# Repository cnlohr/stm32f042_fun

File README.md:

# stm32f042_fun

My fun repo for the STM32f042.  Feel free to rifle through.  All the projects are incomplete, but mostly work.

Check out my IO list: https://docs.google.com/spreadsheets/d/1DyMCKiVg4tmwGgn1U_OD7lgiobow0eRoh-zJ0Q15YpQ/edit?usp=sharing

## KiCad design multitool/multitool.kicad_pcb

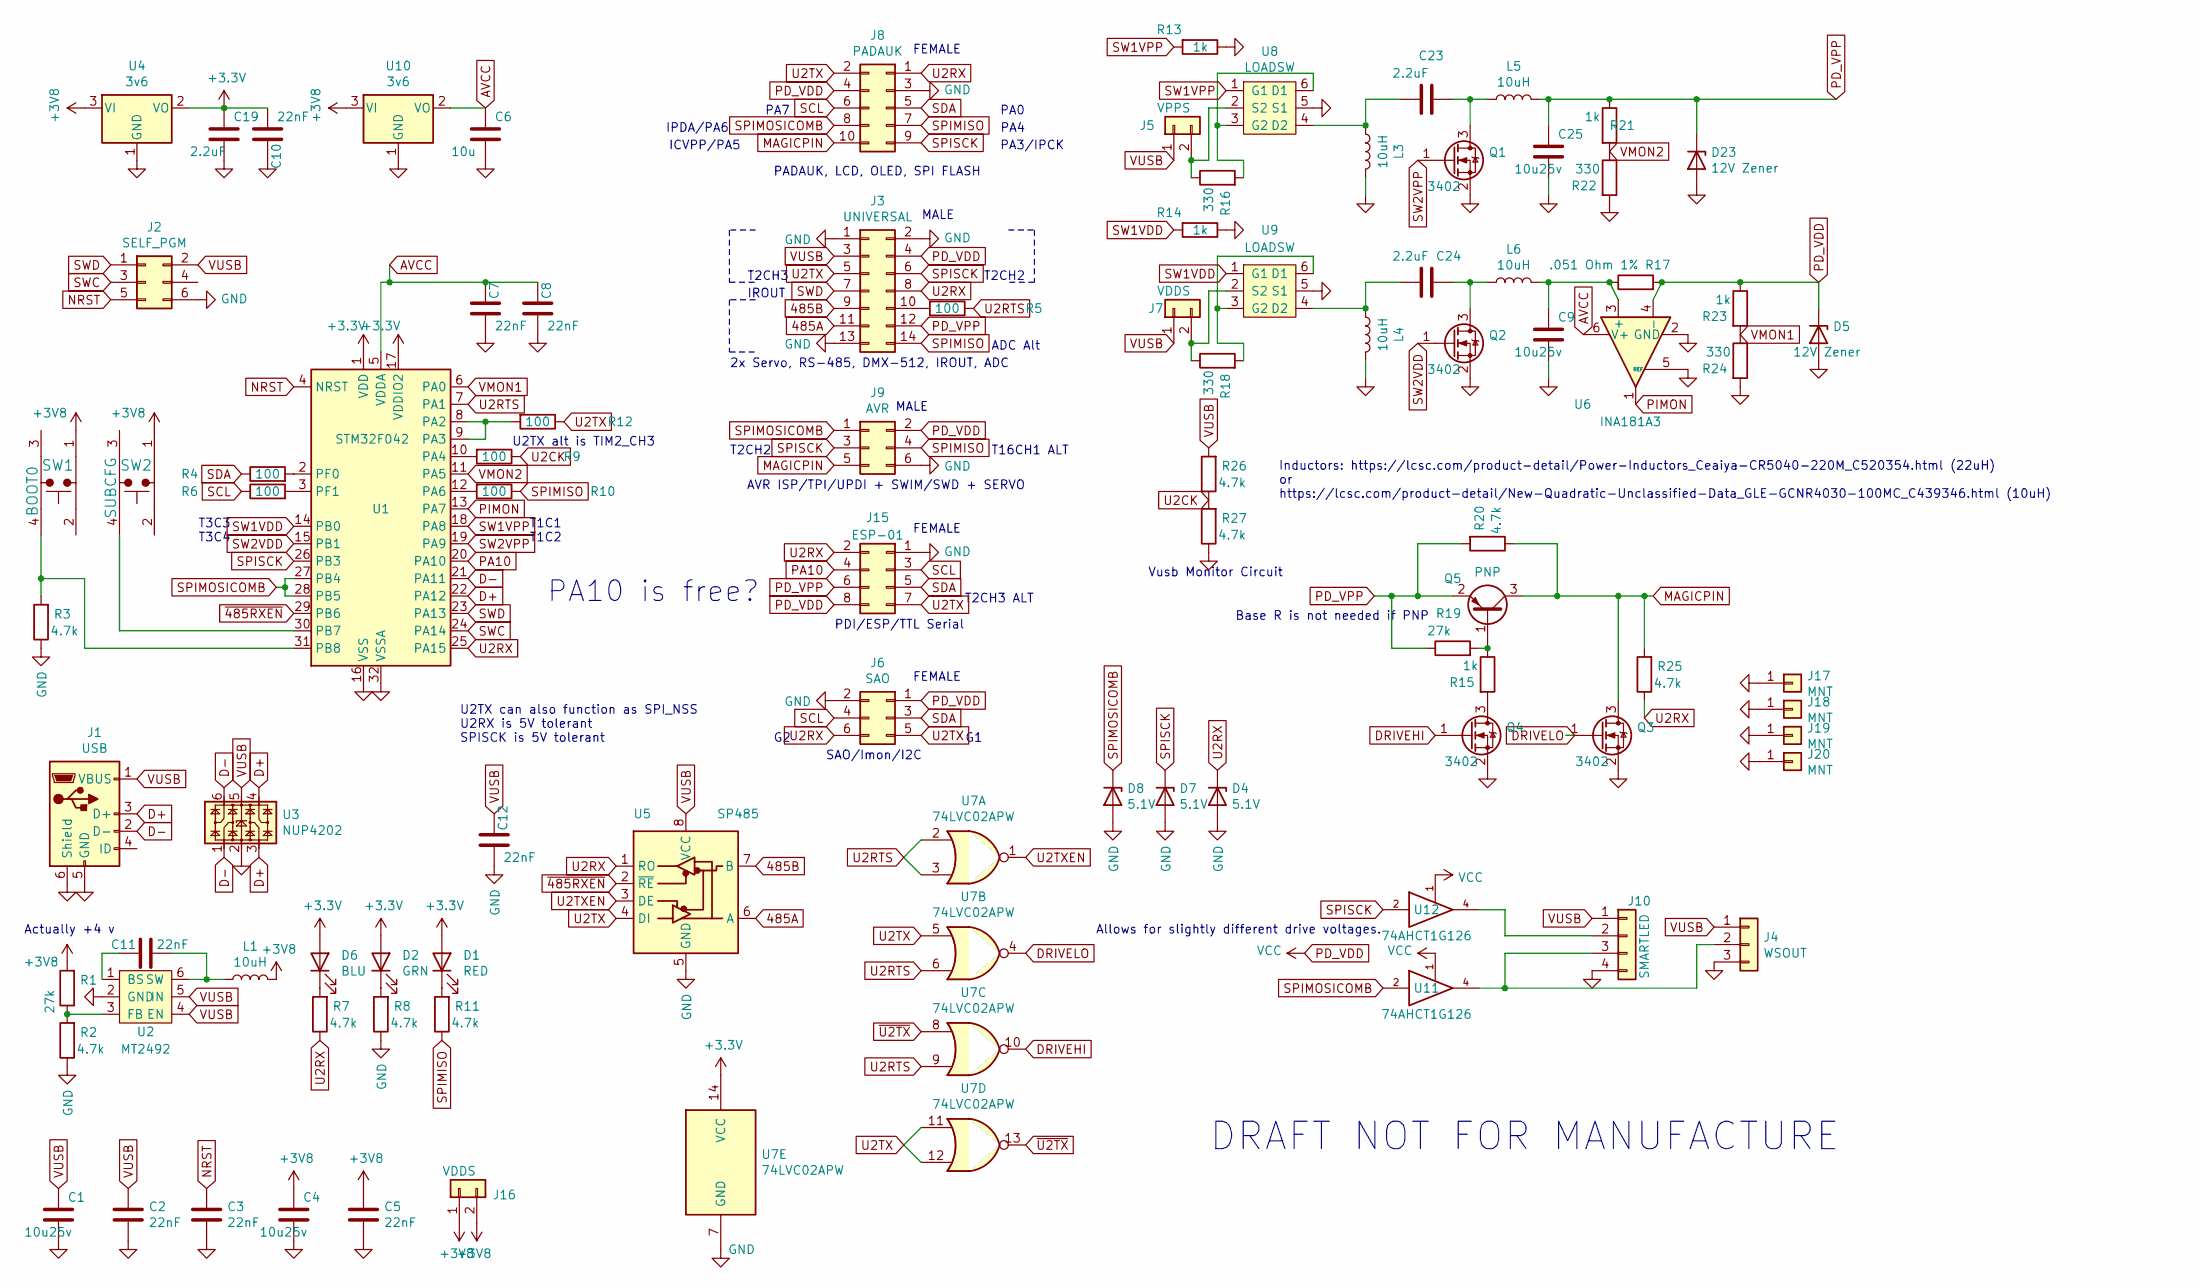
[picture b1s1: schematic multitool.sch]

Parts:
C1, C4, C9, C25: 10u25v; C_0805_2012Metric_Pad1.15x1.40mm_HandSolder
C2, C3, C5, C7, C8, C10, C11, C12: 22nF; C_0603_1608Metric
C6: 10u; C_0805_2012Metric_Pad1.15x1.40mm_HandSolder
C19, C23, C24: 2.2uF; C_0805_2012Metric_Pad1.15x1.40mm_HandSolder
D1: RED; LED_0805_2012Metric_Pad1.15x1.40mm_HandSolder
D2: GRN; LED_0805_2012Metric_Pad1.15x1.40mm_HandSolder
D4, D7, D8: 5.1V; D_SOD-123
D5, D23: 12V Zener; D_SOD-123
D6: BLU; LED_0805_2012Metric_Pad1.15x1.40mm_HandSolder
J1: USB; chinausb-multi
J2: SELF_PGM; RIBBON6SMT_POGO_OR_IDC
J3: UNIVERSAL; PinHeader_2x07_P2.54mm_Vertical_SMD
J4: WSOUT; PinHeader_1x03_P2.54mm_Vertical_SMD_Pin1Left
J5: VPPS; SolderJumper-2_P1.3mm_Bridged_Pad1.0x1.5mm
J6: SAO; PinSocket_2x03_P2.54mm_Vertical_SMD
J7, J16: VDDS; SolderJumper-2_P1.3mm_Bridged_Pad1.0x1.5mm
J8: PADAUK; PinSocket_2x05_P2.54mm_Vertical_SMD
J9: AVR; PinHeader_2x03_P2.54mm_Vertical_SMD
J10: SMARTLED; PinHeader_1x04_P2.54mm_Vertical_SMD_Pin1Left
J15: ESP-01; PinSocket_2x04_P2.54mm_Vertical_SMD
J17, J18, J19, J20: MNT; MountingHole_5.3mm_M5_Pad_Via
L1, L3, L4, L5, L6: 10uH; L_2816_7142Metric
Q1, Q2, Q3, Q4: 3402; SOT-23
Q5: PNP; SOT-23
R1, R19: 27k; R_0603_1608Metric
R2, R3, R7, R8, R11, R20, R25, R26, R27: 4.7k; R_0603_1608Metric
R4, R5, R6, R9, R10, R12: 100; R_0603_1608Metric
R13, R14, R15, R21, R23: 1k; R_0603_1608Metric
R16, R18, R22, R24: 330; R_0603_1608Metric
R17: .051 Ohm 1%; R_0805_2012Metric_Pad1.15x1.40mm_HandSolder
SW1: BOOT0; TACTILE10B
SW2: SUBCFG; TACTILE10B
U1: STM32F042; TQFP-32_7x7mm_P0.8mm
U2: MT2492; SOT-23-6_Handsoldering
U3: NUP4202; SOT-363_SC-70-6
U4, U10: 3v6; SOT-23
U5: SP485; SOP-8_3.9x4.9mm_P1.27mm
U6: INA181A3; SOT-23-6
U7: 74LVC02APW; TSSOP-14_4.4x5mm_P0.65mm
U8, U9: LOADSW; SOT-23-6
U11, U12: 74AHCT1G126; SOT-23-6

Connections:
485A: J3.11, U5.6 (A)
485B: J3.9, U5.7 (B)
+3V3: C10.2, C19.1, D1.2 (A), D2.2 (A), D6.2 (A), U1.1 (VDD), U1.17 (VDDIO2), U4.2 (VO), U7.14 (VCC)
+3V8: C4.1, C5.1, J16.1, J16.2, L1.2, R1.2, SW1.1, SW2.1, U4.3 (VI), U10.3 (VI)
AVCC: C6.1, C7.1, C8.1, U1.5 (VDDA), U6.6 (V+), U10.2 (VO)
D+: J1.3 (D+), U1.22 (PA12), U3.3, U3.4
D-: J1.2 (D-), U1.21 (PA11), U3.1, U3.6
DRIVEHI: Q4.1 (G), U7.10
DRIVELO: Q3.1 (G), U7.4
MAGICPIN: J8.10, J9.5, Q3.3 (D), Q5.3 (C), R20.1, R25.2
NRST: C3.1, J2.5, U1.4 (NRST)
unnamed: C9.1, L6.2, R17.1, U6.3 (+)
unnamed: C11.1, U2.1 (BS)
unnamed: C11.2, L1.1, U2.6 (SW)
unnamed: C23.1, L5.1, Q1.3 (D)
unnamed: C23.2, L3.1, U8.4 (D2)
unnamed: C24.1, L6.1, Q2.3 (D)
unnamed: C24.2, L4.1, U9.4 (D2)
unnamed: D1.1 (K), R11.2
unnamed: D2.1 (K), R8.2
unnamed: D6.1 (K), R7.2
unnamed: J3.10, R5.2
unnamed: J5.2, R16.1, U8.2 (S2)
unnamed: J7.2, R18.1, U9.2 (S2)
unnamed: J10.2, U12.4
unnamed: J4.2, J10.3, U11.4
unnamed: Q4.3 (D), R15.2
unnamed: Q5.1 (B), R15.1, R19.2
unnamed: R1.1, R2.2, U2.3 (FB)
unnamed: R3.2, SW1.4, U1.31 (PB8)
unnamed: R4.2, U1.2 (PF0)
unnamed: R6.2, U1.3 (PF1)
unnamed: R9.2, U1.10 (PA4)
unnamed: R10.2, U1.12 (PA6)
unnamed: R12.2, U1.8 (PA2), U1.9 (PA3)
unnamed: R16.2, U8.3 (G2), U8.6 (D1)
unnamed: R18.2, U9.3 (G2), U9.6 (D1)
unnamed: SW2.4, U1.30 (PB7)
PD_VDD: D5.1 (K), J3.4, J6.1, J8.4, J9.2, J15.8, R17.2, R23.1, U6.4 (-), U11.1, U11.5 (VCC), U12.1, U12.5 (VCC)
PD_VPP: C25.1, D23.1 (K), J3.12, J15.6, L5.2, Q5.2 (E), R19.1, R20.2, R21.1
PIMON: U1.13 (PA7), U6.1
SCL: J6.4, J8.6, J15.3, R6.1
SDA: J6.3, J8.5, J15.5, R4.1
SPIMOSICOMB: D8.1 (K), J8.8, J9.1, U1.27 (PB4), U1.28 (PB5), U11.2
SPISCK: D7.1 (K), J3.6, J8.9, J9.3, U1.26 (PB3), U12.2
SW1VDD: R14.2, U1.14 (PB0), U9.1 (G1)
SW1VPP: R13.2, U1.18 (PA8), U8.1 (G1)
SW2VDD: Q2.1 (G), U1.15 (PB1)
SW2VPP: Q1.1 (G), U1.19 (PA9)
SWC: J2.3, U1.24 (PA14)
SWD: J2.1, J3.7, U1.23 (PA13)
U2RTS: R5.1, U1.7 (PA1), U7.2, U7.3, U7.6, U7.9
U2RX: D4.1 (K), J3.8, J6.6, J8.1, J15.2, R7.1, R25.1, U1.25 (PA15), U5.1 (RO)
U2TX: J3.5, J6.5, J8.2, J15.7, R12.1, U5.4 (DI), U7.5, U7.11, U7.12
U2TXEN: U5.3 (DE), U7.1
VMON1: R23.2, R24.1, U1.6 (PA0)
VMON2: R21.2, R22.1, U1.11 (PA5)
VUSB: C1.1, C2.1, C12.1, J1.1 (VBUS), J2.2, J3.3, J4.1, J5.1, J7.1, J10.1, R26.2, U2.4 (EN), U2.5 (IN), U3.5, U5.8 (VCC)
~485RXEN~: U1.29 (PB6), U5.2 (~RE)
~U2TX~: U7.8, U7.13

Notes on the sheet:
Actually +4 v
DRAFT NOT FOR MANUFACTURE
U2TX can also function as SPI_NSS U2RX is 5V tolerant SPISCK is 5V tolerant
AVR ISP/TPI/UPDI + SWIM/SWD + SERVO
PDI/ESP/TTL Serial
2x Servo, RS-485, DMX-512, IROUT, ADC
T16CH1 ALT
U2TX alt is TIM2_CH3
T2CH3 ALT
T1C1 T1C2
T3C3 T3C4
SAO/Imon/I2C
PA7
IPDA/PA6
PA0
ICVPP/PA5
PA4
PA3/IPCK
Base R is not needed if PNP
T2CH2
MALE
FEMALE
T2CH3
PADAUK, LCD, OLED, SPI FLASH
Vusb Monitor Circuit
Inductors: https://lcsc.com/product-detail/Power-Inductors_Ceaiya-CR5040-220M_C520354.html (22uH) or https://lcsc.com/product-detail/New-Quadratic-Unclassified-Data_GLE-GCNR4030-100MC_C439346.html (10uH)
IROUT
Allows for slightly different drive voltages.
PA10 is free?
ADC Alt

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
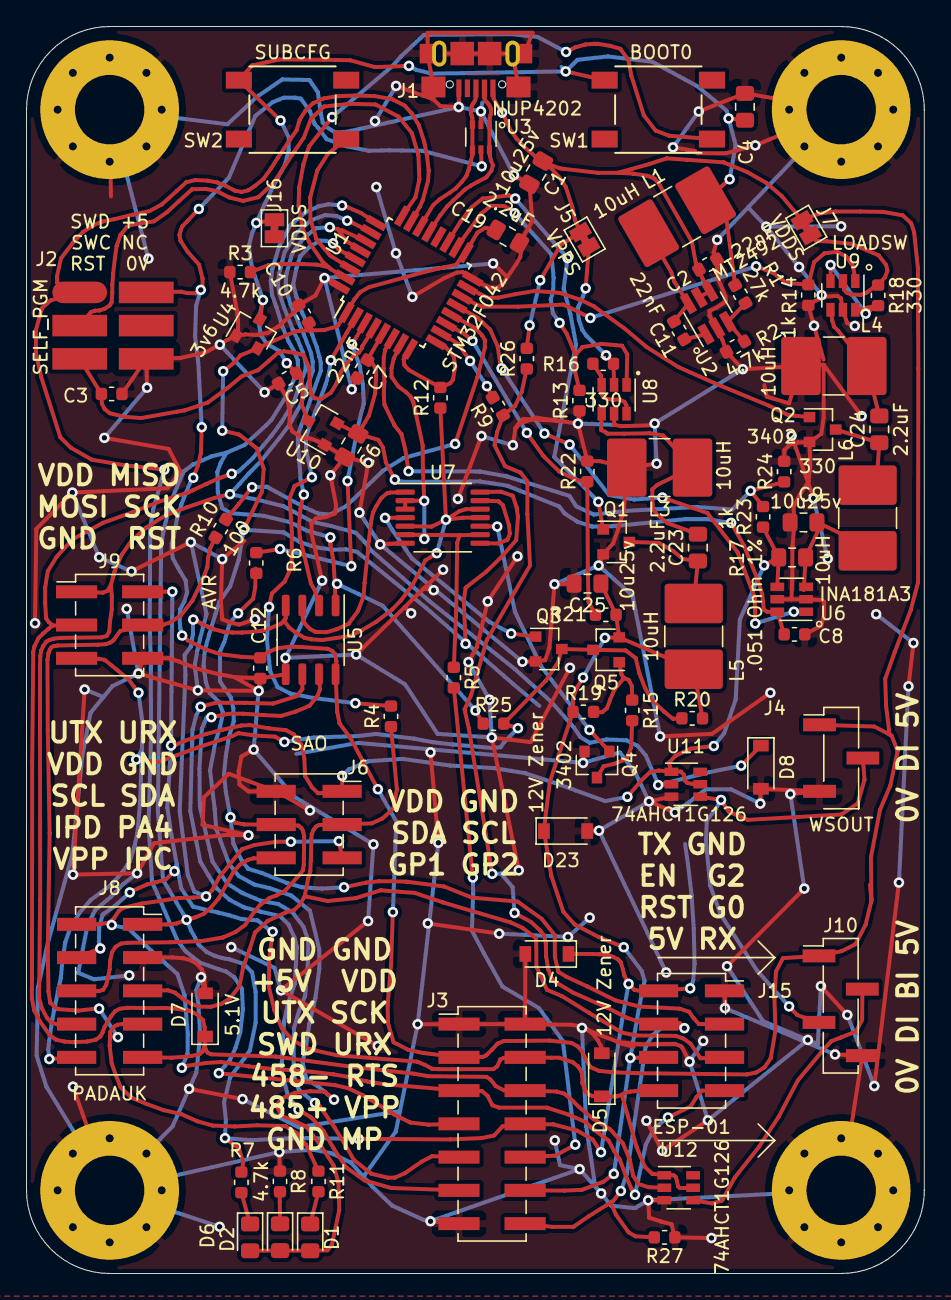
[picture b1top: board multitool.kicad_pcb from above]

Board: 2 copper layers, 68.6 x 95.3 mm, 91 parts (0 on the bottom side), 63 nets.

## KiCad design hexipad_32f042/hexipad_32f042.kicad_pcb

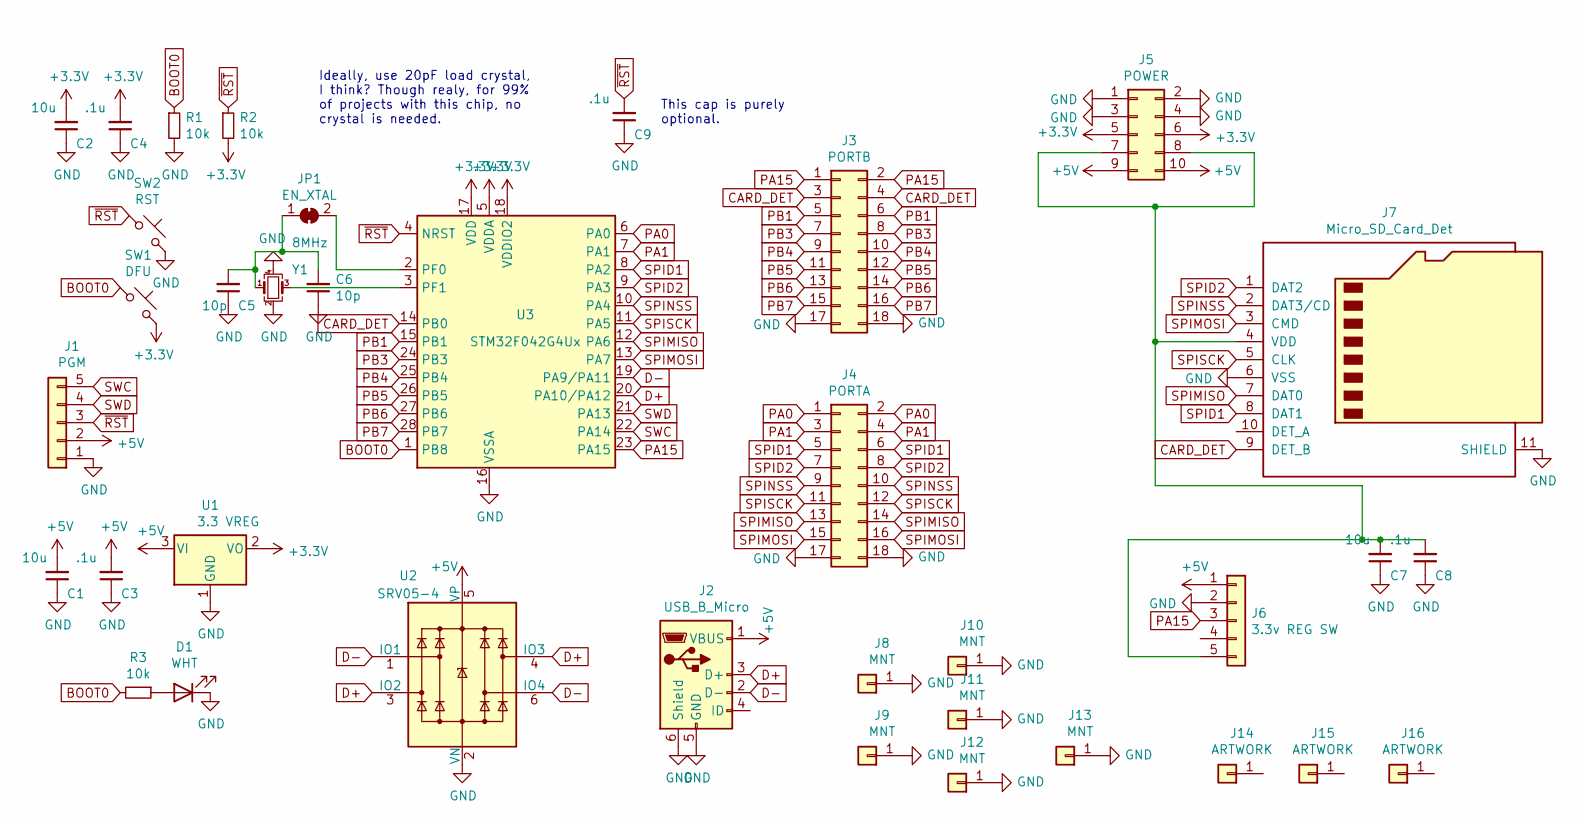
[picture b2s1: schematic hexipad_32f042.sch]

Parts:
C1, C2, C7: 10u; C_0603_1608Metric
C3, C4, C8, C9: .1u; C_0603_1608Metric
C5, C6: 10p; C_0603_1608Metric
D1: WHT; D_0603_1608Metric
J1: PGM; POGO-5
J2: USB_B_Micro; chinausb-multi
J3: PORTB; PinHeader_2x09_P2.54mm_Vertical_SMD
J4: PORTA; PinHeader_2x09_P2.54mm_Vertical_SMD
J5: POWER; PinHeader_2x05_P2.54mm_Vertical_SMD
J6: 3.3v REG SW; SOT-23-5
J7: Micro_SD_Card_Det; MicroSD-HYC77-TF09-200
J8, J9, J10, J11, J12, J13: MNT; stm32f042_breakout_pin
J14: ARTWORK; back-artwork-cristabelle-braden-vsmall
J15: ARTWORK; leaves_front-cristabelle
J16: ARTWORK; cb-signature
JP1: EN_XTAL; SolderJumper-2_P1.3mm_Bridged_RoundedPad1.0x1.5mm
R1, R2, R3: 10k; R_0603_1608Metric
SW1: DFU; SW_SPST_EVPBF
SW2: RST; SW_SPST_EVPBF
U1: 3.3 VREG; SOT-23
U2: SRV05-4; SOT-23-6
U3: STM32F042G4Ux; QFN-28_4x4mm_P0.5mm
Y1: 8MHz; Crystal_SMD_3225-4Pin_3.2x2.5mm

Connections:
+3V3: C2.2, C4.2, J5.5, J5.6, R2.2, SW1.2, U1.2 (VO), U3.5 (VDDA), U3.17 (VDD), U3.18 (VDDIO2)
+5V: C1.2, C3.2, J1.2, J2.1 (VBUS), J5.9, J5.10, J6.1, U1.3 (VI), U2.5 (VP)
BOOT0: R1.1, R3.2, SW1.1, U3.1 (PB8)
CARD_DET: J3.3, J3.4, J7.9 (DET_B), U3.14 (PB0)
D+: J2.3 (D+), U2.3 (IO2), U2.4 (IO3), U3.20 (PA10/PA12)
D-: J2.2 (D-), U2.1 (IO1), U2.6 (IO4), U3.19 (PA9/PA11)
GND: C1.1, C2.1, C3.1, C4.1, C5.1, C6.1, C7.1, C8.1, C9.1, D1.1 (K), J1.1, J2.5 (GND), J2.6 (Shield), J3.17, J3.18, J4.17, J4.18, J5.1, J5.2, J5.3, J5.4, J6.2, J7.6 (VSS), J7.11 (SHIELD), J8.1, J9.1, J10.1, J11.1, J12.1, J13.1, R1.2, SW2.2, U1.1 (GND), U2.2 (VN), U3.16 (VSSA), Y1.2, Y1.4
unnamed: C5.2, C6.2, JP1.1 (A), Y1.1
unnamed: C7.2, C8.2, J5.7, J5.8, J6.5, J7.4 (VDD)
unnamed: D1.2 (A), R3.1
unnamed: JP1.2 (B), U3.2 (PF0)
unnamed: U3.3 (PF1), Y1.3
PA0: J4.1, J4.2, U3.6 (PA0)
PA1: J4.3, J4.4, U3.7 (PA1)
PA15: J3.1, J3.2, J6.3, U3.23 (PA15)
PB1: J3.5, J3.6, U3.15 (PB1)
PB3: J3.7, J3.8, U3.24 (PB3)
PB4: J3.9, J3.10, U3.25 (PB4)
PB5: J3.11, J3.12, U3.26 (PB5)
PB6: J3.13, J3.14, U3.27 (PB6)
PB7: J3.15, J3.16, U3.28 (PB7)
SPID1: J4.5, J4.6, J7.8 (DAT1), U3.8 (PA2)
SPID2: J4.7, J4.8, J7.1 (DAT2), U3.9 (PA3)
SPIMISO: J4.13, J4.14, J7.7 (DAT0), U3.12 (PA6)
SPIMOSI: J4.15, J4.16, J7.3 (CMD), U3.13 (PA7)
SPINSS: J4.9, J4.10, J7.2 (DAT3/CD), U3.10 (PA4)
SPISCK: J4.11, J4.12, J7.5 (CLK), U3.11 (PA5)
SWC: J1.5, U3.22 (PA14)
SWD: J1.4, U3.21 (PA13)
~RST~: C9.2, J1.3, R2.1, SW2.1, U3.4 (NRST)

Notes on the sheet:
Ideally, use 20pF load crystal, I think? Though realy, for 99% of projects with this chip, no crystal is needed.
This cap is purely optional.

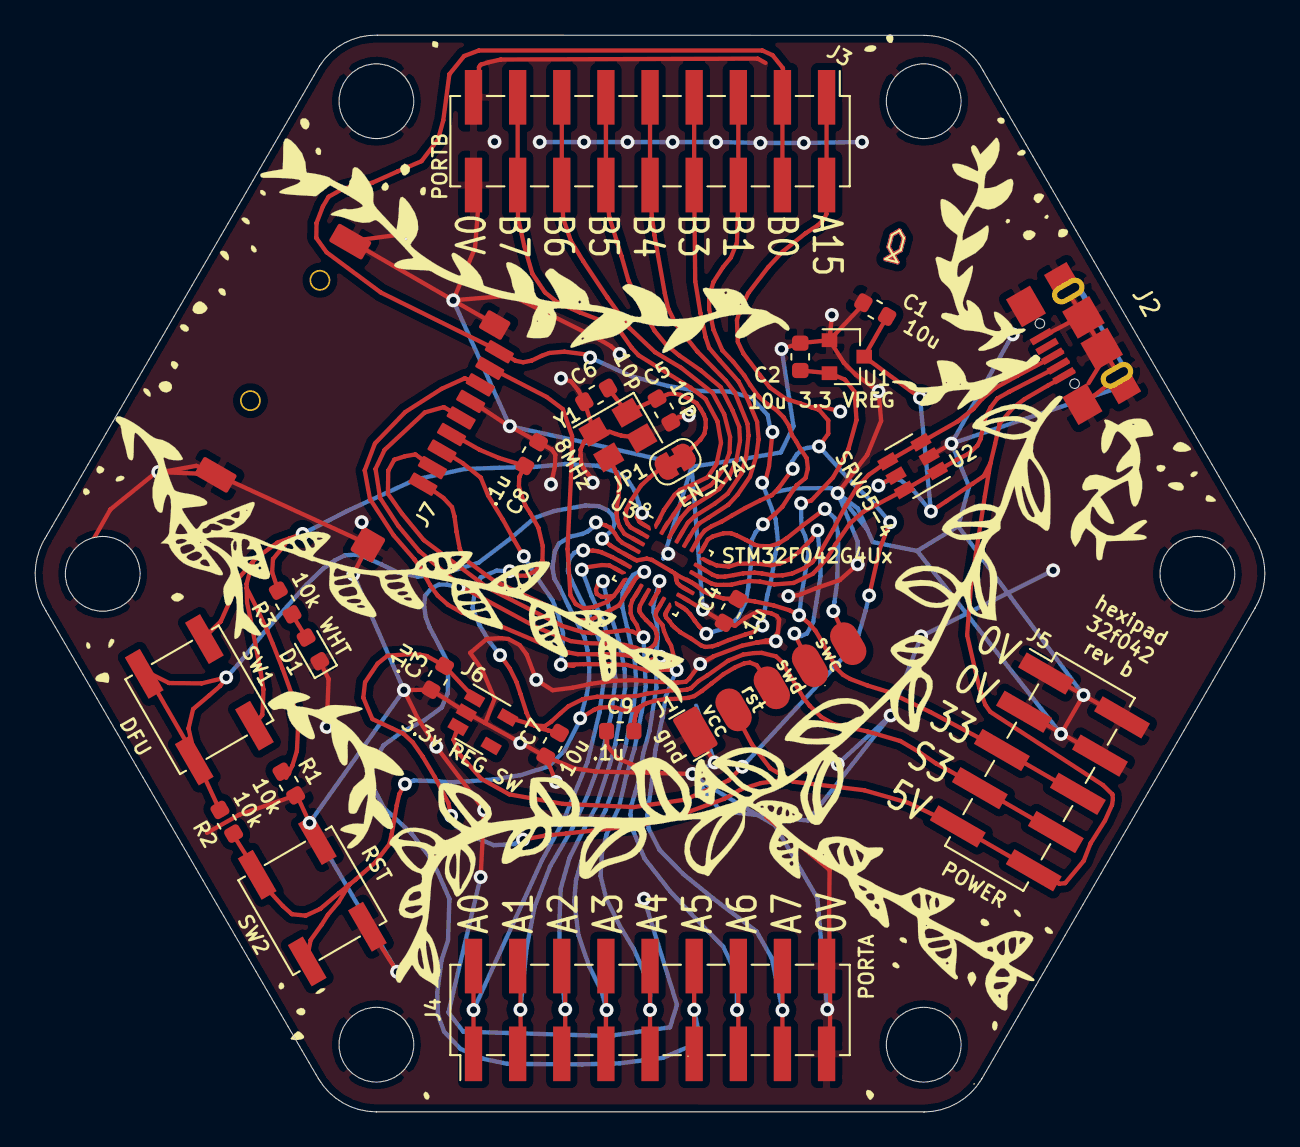
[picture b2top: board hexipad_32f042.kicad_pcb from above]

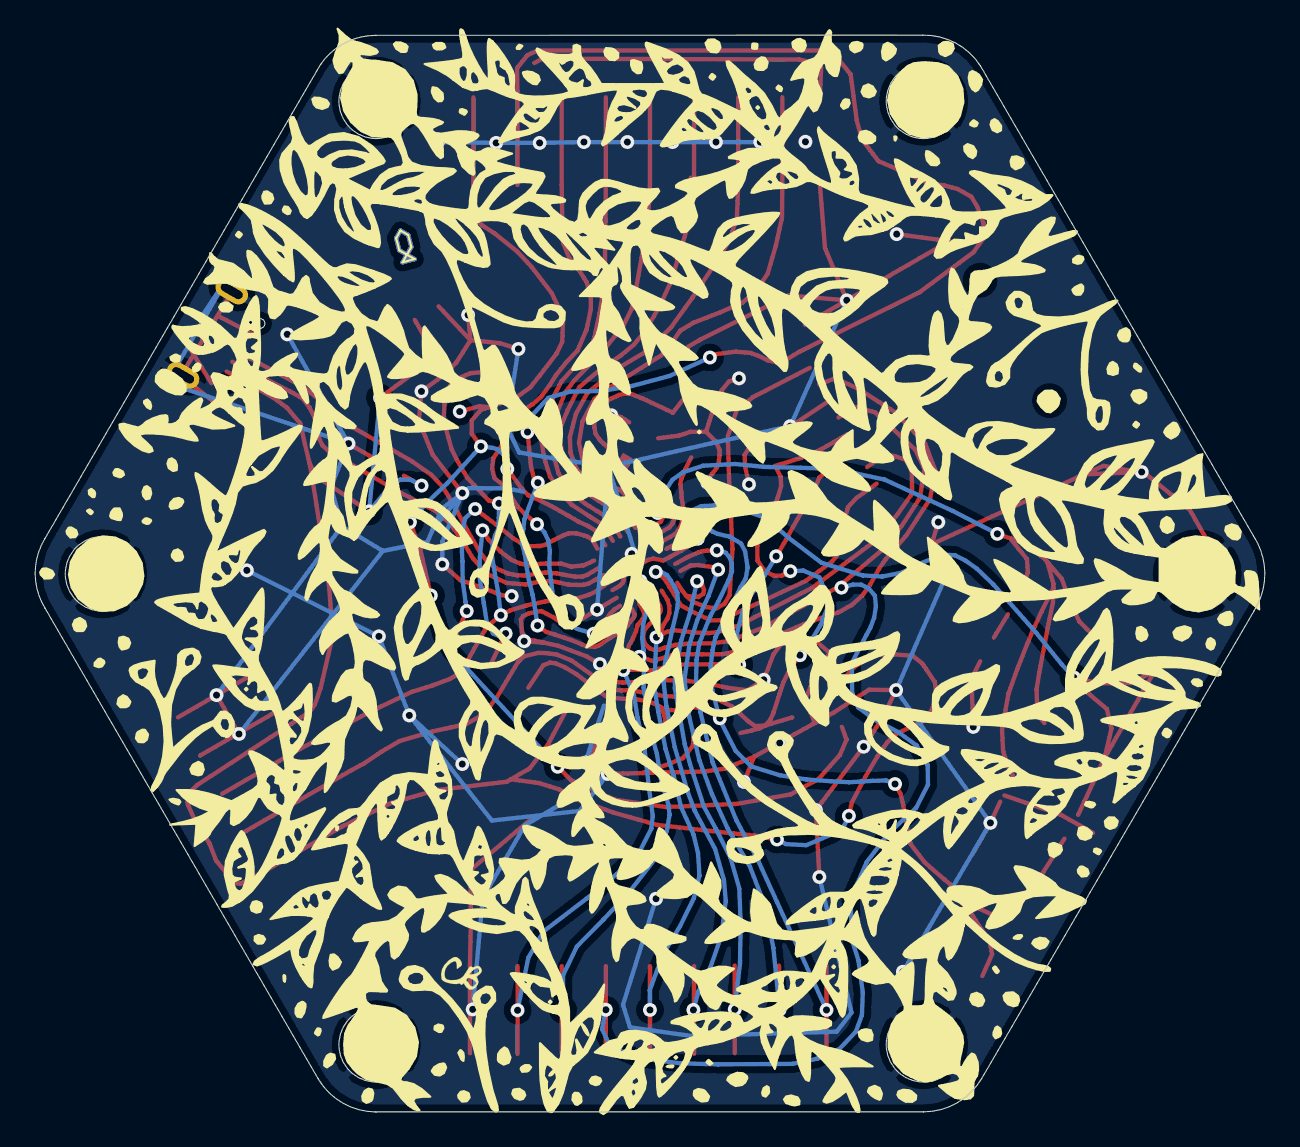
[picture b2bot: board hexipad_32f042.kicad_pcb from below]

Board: 2 copper layers, 70.8 x 62.0 mm, 36 parts (2 on the bottom side), 30 nets.

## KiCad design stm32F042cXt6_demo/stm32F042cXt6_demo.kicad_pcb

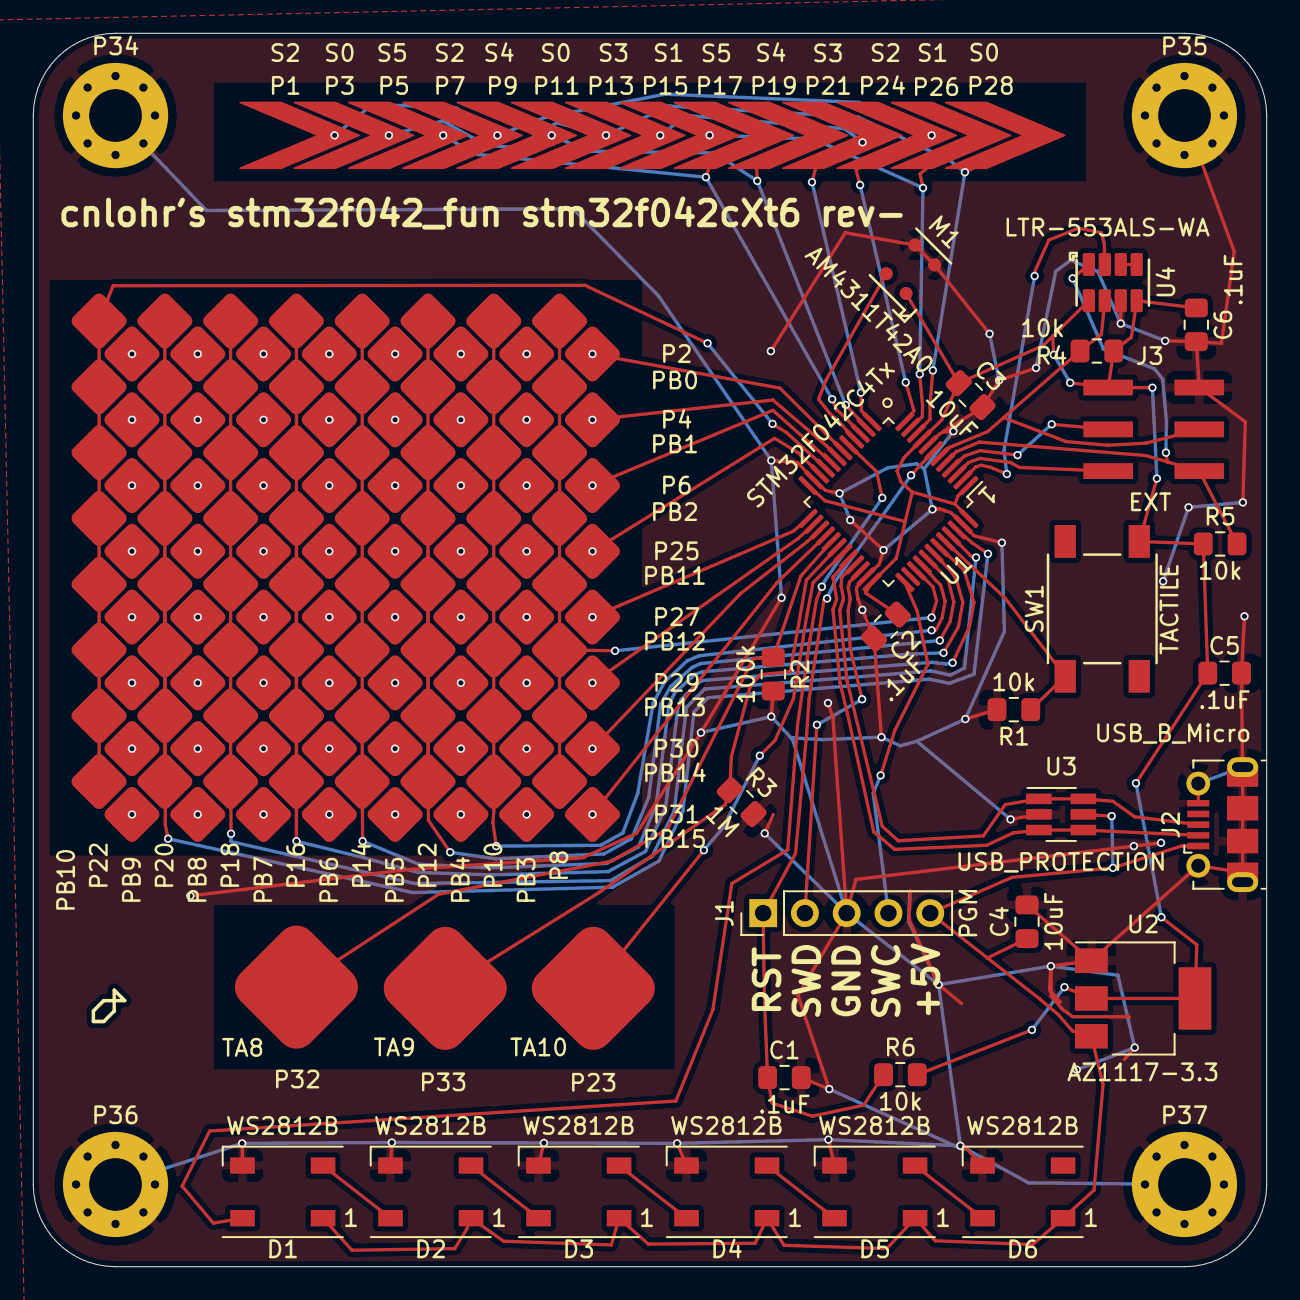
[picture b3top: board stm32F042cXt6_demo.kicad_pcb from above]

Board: 2 copper layers, 75.0 x 75.0 mm, 64 parts (0 on the bottom side), 47 nets.

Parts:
C1, C2, C5, C6: .1uF; C_0805_2012Metric_Pad1.15x1.40mm_HandSolder
C3, C4: 10uF; C_0805_2012Metric_Pad1.15x1.40mm_HandSolder
D1, D2, D3, D4, D5, D6: WS2812B; LED_WS2812B_PLCC4_5.0x5.0mm_P3.2mm
J1: PGM; PinHeader_1x05_P2.54mm_Vertical
J2: USB_B_Micro; USB_Micro-B_Molex-105017-0001
J3: EXT; RIBBON6SMT
M1: AM4311T42A0; PATRON-MIC-AM4311T42A0
P1, P7, P24: S2; TOUCH_SLIDER_CHEVRON
P2: PB0; TOUCH_ARRAY_8_BOT
P3, P11, P28: S0; TOUCH_SLIDER_CHEVRON
P4: PB1; TOUCH_ARRAY_8_BOT
P5, P17: S5; TOUCH_SLIDER_CHEVRON
P6: PB2; TOUCH_ARRAY_8_BOT
P8: PB3; TOUCH_ARRAY_8_TOP
P9, P19: S4; TOUCH_SLIDER_CHEVRON
P10: PB4; TOUCH_ARRAY_8_TOP
P12: PB5; TOUCH_ARRAY_8_TOP
P13, P21: S3; TOUCH_SLIDER_CHEVRON
P14: PB6; TOUCH_ARRAY_8_TOP
P15, P26: S1; TOUCH_SLIDER_CHEVRON
P16: PB7; TOUCH_ARRAY_8_TOP
P18: PB8; TOUCH_ARRAY_8_TOP
P20: PB9; TOUCH_ARRAY_8_TOP
P22: PB10; TOUCH_ARRAY_8_TOP
P23: TA10; TOUCH_MARK
P25: PB11; TOUCH_ARRAY_8_BOT
P27: PB12; TOUCH_ARRAY_8_BOT
P29: PB13; TOUCH_ARRAY_8_BOT
P30: PB14; TOUCH_ARRAY_8_BOT
P31: PB15; TOUCH_ARRAY_8_BOT
P32: TA8; TOUCH_MARK
P33: TA9; TOUCH_MARK
P34, P35, P36, P37: CONN_1; MountingHole_3.2mm_M3_Pad_Via
R1, R4, R5, R6: 10k; R_0805_2012Metric_Pad1.15x1.40mm_HandSolder
R2: 100k; R_0805_2012Metric_Pad1.15x1.40mm_HandSolder
R3: 1M; R_0805_2012Metric_Pad1.15x1.40mm_HandSolder
SW1: TACTILE; TACTILE10B
U1: STM32F042C4Tx; LQFP-48_7x7mm_P0.5mm
U2: AZ1117-3.3; SOT-223-3_TabPin2
U3: USB_PROTECTION; SOT-23-6_Handsoldering
U4: LTR-553ALS-WA; LTR-553ALS-WA-LITE-ON-AMBIENT

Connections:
+3V3: C2.1, C3.1, C5.1, C6.1, J3.6, M1.1, R4.1, R5.1, R6.2, SW1.4, U1.1, U1.9, U1.24, U1.36, U1.48, U2.2, U4.5, U4.8
+5V: C4.1, D1.1, D2.1, D3.1, D4.1, D5.1, D6.1, J1.5, J2.1, U2.3, U3.5
ADC: M1.4, U1.16
BOOT0: R1.1, SW1.1, U1.44
D+: J2.3, U1.33, U3.1, U3.6
D-: J2.2, U1.32, U3.3, U3.4
GND: C1.2, C2.2, C3.2, C4.2, C5.2, C6.2, D1.3, D2.3, D3.3, D4.3, D5.3, D6.3, J1.3, J2.5, J2.6, J3.5, M1.2, M1.3, P34.1, P35.1, P36.1, P37.1, R1.2, R2.2, R3.2, U1.8, U1.23, U1.35, U1.47, U2.1, U3.2, U4.6
unnamed: D1.2, D2.4
unnamed: D2.2, D3.4
unnamed: D3.2, D4.4
unnamed: D4.2, D5.4
unnamed: D5.2, D6.4
unnamed: P2.1, U1.18
unnamed: P4.1, U1.19
unnamed: P6.1, U1.20
unnamed: P8.1, U1.39
unnamed: P10.1, U1.40
unnamed: P12.1, U1.41
unnamed: P14.1, U1.42
unnamed: P16.1, U1.43
unnamed: P18.1, U1.45
unnamed: P20.1, U1.46
unnamed: P22.1, U1.21
unnamed: P23.1, U1.31
unnamed: P25.1, U1.22
unnamed: P27.1, U1.25
unnamed: P29.1, U1.26
unnamed: P30.1, U1.27
unnamed: P31.1, U1.28
unnamed: U4.3, U4.4
PC13: U1.2, U4.2
PC14: J3.2, U1.3
PC15: J3.4, U1.4
RESET: C1.1, J1.1, R6.1, U1.7
SCL: J3.3, R4.2, U1.6, U4.7
SDA: J3.1, R5.2, U1.5, U4.1
SLIDER0: P3.1, P11.1, P28.1, U1.10
SLIDER1: P15.1, P26.1, U1.11
SLIDER2: P1.1, P7.1, P24.1, U1.12
SLIDER3: P13.1, P21.1, U1.13
SLIDER4: P9.1, P19.1, U1.14
SLIDER5: P5.1, P17.1, U1.15
SWC: J1.4, U1.37
SWD: J1.2, U1.34
TMPA8: P32.1, R2.1, U1.29
TMPA9: P33.1, R3.1, U1.30
WS2812: D1.4, U1.17

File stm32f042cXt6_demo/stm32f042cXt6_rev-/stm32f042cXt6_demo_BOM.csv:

Reference,Value,Footprint,LCSC
C1,.1uF,Capacitor_SMD:C_0805_2012Metric_Pad1.15x1.40mm_HandSolder,USE_STOCK
C2,.1uF,Capacitor_SMD:C_0805_2012Metric_Pad1.15x1.40mm_HandSolder,USE_STOCK
C5,.1uF,Capacitor_SMD:C_0805_2012Metric_Pad1.15x1.40mm_HandSolder,USE_STOCK
C6,.1uF,Capacitor_SMD:C_0805_2012Metric_Pad1.15x1.40mm_HandSolder,USE_STOCK
C3,10uF,Capacitor_SMD:C_0805_2012Metric_Pad1.15x1.40mm_HandSolder,USE_STOCK
C4,10uF,Capacitor_SMD:C_0805_2012Metric_Pad1.15x1.40mm_HandSolder,USE_STOCK
D1,WS2812B,LED_SMD:LED_WS2812B_PLCC4_5.0x5.0mm_P3.2mm,https://lcsc.com/product-detail/Light-Emitting-Diodes-LED_Wo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
D2,WS2812B,LED_SMD:LED_WS2812B_PLCC4_5.0x5.0mm_P3.2mm,https://lcsc.com/product-detail/Light-Emitting-Diodes-LED_Wo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
D3,WS2812B,LED_SMD:LED_WS2812B_PLCC4_5.0x5.0mm_P3.2mm,https://lcsc.com/product-detail/Light-Emitting-Diodes-LED_Wo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
D4,WS2812B,LED_SMD:LED_WS2812B_PLCC4_5.0x5.0mm_P3.2mm,https://lcsc.com/product-detail/Light-Emitting-Diodes-LED_Wo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
D5,WS2812B,LED_SMD:LED_WS2812B_PLCC4_5.0x5.0mm_P3.2mm,https://lcsc.com/product-detail/Light-Emitting-Diodes-LED_Wo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
D6,WS2812B,LED_SMD:LED_WS2812B_PLCC4_5.0x5.0mm_P3.2mm,https://lcsc.com/product-detail/Light-Emitting-Diodes-LED_Wo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
J3,EXT,kicad:RIBBON6SMT,https://lcsc.com/product-detail/Pin-Header-Female-Header_BOO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
J1,PGM,Connector_PinHeader_2.54mm:PinHeader_1x05_P2.54mm_Vertical,https://lcsc.com/product-detail/Pin-Header-Female-Header_MIN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
J2,USB_B_Micro,Connector_USB:USB_Micro-B_Molex-105017-0001,https://lcsc.com/product-detail/USB-Connectors_SHOU-HAN-MICR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
M1,AM4311T42A0,kicad:PATRON-MIC-AM4311T42A0,https://lcsc.com/product-detail/Electret-Condenser-Microphon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
R2,100k,Resistor_SMD:R_0805_2012Metric_Pad1.15x1.40mm_HandSolder,USE_STOCK
R1,10k,Resistor_SMD:R_0805_2012Metric_Pad1.15x1.40mm_HandSolder,USE_STOCK
R4,10k,Resistor_SMD:R_0805_2012Metric_Pad1.15x1.40mm_HandSolder,USE_STOCK
R5,10k,Resistor_SMD:R_0805_2012Metric_Pad1.15x1.40mm_HandSolder,USE_STOCK
R6,10k,Resistor_SMD:R_0805_2012Metric_Pad1.15x1.40mm_HandSolder,USE_STOCK
R3,1M,Resistor_SMD:R_0805_2012Metric_Pad1.15x1.40mm_HandSolder,USE_STOCK
SW1,TACTILE,kicad:TACTILE10B,https://lcsc.com/product-detail/Tactile-Switches_SHOU-HAN-TS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
U2,AMS1117-3.3,Package_TO_SOT_SMD:SOT-223-3_TabPin2,https://lcsc.com/product-detail/Low-Dropout-Regulators-LDO_S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
U4,LTR-553ALS-WA,kicad:LTR-553ALS-WA-LITE-ON-AMBIENT,https://lcsc.com/product-detail/New-Arrivals_Lite-On-LTR-553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
U1,STM32F042C4Tx,Package_QFP:LQFP-48_7x7mm_P0.5mm,https://lcsc.com/product-detail/ST-Microelectronics_STMicroe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
U3,USB_PROTECTION,Package_TO_SOT_SMD:SOT-23-6_Handsoldering,https://lcsc.com/product-detail/TVS_Silergy_CS0816_CS0816_C1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

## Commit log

2020-03-13 bump
2020-03-14 Fix capitalization
2020-03-14 Fix names
2020-05-07 Add some firmware
2020-05-31 Working on a new multitool
2020-05-31 Add multitool
2020-05-31 Add untested note
2020-05-31 Getting closer
2020-05-31 Add a synchronous zeta converter simulation.
2020-06-02 update some tweaks to the zeta sim thoughts.
2020-06-02 Tweak multitool design.
2020-06-03 add ALS I2C example
2020-06-03 Forgot to bump design
2020-06-03 fix module names
2020-06-03 Bump design - showing the 5V Vusb monitor
2020-06-04 Progress on multitool
2020-07-23 bump design
2020-07-25 Add the breakout, as printed.
2020-08-06 Trying to get this puppy off the ground :(... Having USB Issues
2020-08-06 forgot to commit epaptest
2020-08-06 Update epaper files
2020-08-06 Update firmware usb file.
2020-08-07 bump revision and rename our breakout to hexipad.
2020-08-07 Correct part #
2020-08-08 Fix up setup functions.
2020-08-21 bump design + Add PDF
2020-08-30 various updates
2020-09-02 Another demo
2020-09-04 Add a 40.6 MHz transmitter.
2020-09-15 add rev B - fix USB
2020-09-16 update multitool.
2020-09-16 another shot at multitool
2020-09-16 Move attempt at can away.
2020-09-17 bump design slightly.
2021-03-03 Fix off by one error in SPI
2021-03-03 Add an example of driving GPIOs with DMA from a timer.
